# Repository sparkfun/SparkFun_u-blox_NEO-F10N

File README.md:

SparkFun GNSS L1/L5 Breakout- NEO-F10N, SMA
========================================

[*SparkFun GNSS L1/L5 Breakout - NEO-F10N, SMA (GPS-24114)*](https://www.sparkfun.com/products/24114)

The SparkFun GNSS L1/L5 Breakout - NEO-F10N, SMA is a standard precision GNSS board with meter-level positional accuracy. The NEO-F10N uses the L1/L5 bands instead of the more commonly seen L1/L2 bands. Utilizing the L5 band, the NEO-F10N delivers improved performance under challenging urban environments. The L5 signals fall within the protected ARNS (aeronautical radio navigation service) frequency band, leading to less RF interference.

This breakout supports the concurrent reception of three GNSS constellations: GPS, Galileo, and BeiDou. The proprietary dual-band multipath mitigation technology from the u-blox F10 allows the module to choose the best signals from both bands to achieve a significantly better position accuracy in challenging urban environments than with the L1 band alone.

What's different from other u-blox modules is that the NEO-F10N module only supports one serial UART communication port. We included a CH340 USB-to-serial converter to connect the board to a computer's USB port easily. For users connecting the board's serial UART pins to a microcontroller or radio, you will need to cut the USB-TX and USB-RX jumpers to avoid bus contention. Pins for power, serial, pulse per second, and control pins are broken out to 0.1"-spaced pins on the board's edge. We have also conveniently included a 1x6 header should you connect a BlueSMiRF v2 to transmit data wirelessly!

The breakout is also has an on-board rechargeable battery that provides power to the RTC on the NEO-F10N. This reduces the time-to-first fix from a cold start (~28s) to a hot start (2s). The battery will maintain RTC and GNSS orbit data without being connected to power for plenty of time. We have included an SMA connector for a secure connection.

U-blox-based GPS products are configurable using the popular but dense Windows program u-center. Plenty of different functions can be configured on the NEO-F10N: baud rates, update rates, spoofing detection, external interrupts, SBAS, etc. To get started, we've included a few basic UART examples with our SparkFun Arduino Library.

Repository Contents
-------------------
* **.github/workflows** - YAML files used for GitHub Actions and GitHub Pages/mkdocs
* **/Hardware** - KiCad design files (.brd, .sch)
  * **/Production** - Production panel files (.brd)
* **/docs** - Online documentation files
  * **/assets** - Folder containing all the file assets used for product documentation
    * **/3d_model** - Exported 3D models from KiCad
    * **/board_files** - Copy of design files used for product documentation
    * **/component_documentation** - Datasheets and manuals for hardware components
    * **/img** - Images for product documentation
  * **/github** - Files stating how to contribute and filing issues used for product documentation
  * **/javascript** - Folder containing custom javascript used for product documentation
  * **/stylesheet** - Folder containing CSS files used for product documentation
* **/overrides** - Customization files used for product documentation
  * **/.icons** - Icons used for GitHub used for product documentation
  * **./partials** - Used for product documentation

Documentation
--------------
* **[Library](https://github.com/sparkfun/SparkFun_u-blox_GNSS_v3)** - Arduino library for u-blox modules.
* **[Hookup Guide](https://docs.sparkfun.com/SparkFun_u-blox_NEO-F10N)** - Basic hookup guide for the NEO-F10N breakout board.

Product Versions
----------------
* [GPS-24114](https://www.sparkfun.com/products/24114) - Initial release

Version History
---------------
* v1.0 - Initial release

License Information
-------------------

This product is _**open source**_!

Please review the LICENSE.md file for license information.

If you have any questions or concerns on licensing, please contact technical support on our [SparkFun forums](https://forum.sparkfun.com/viewforum.php?f=152).

Distributed as-is; no warranty is given.

- Your friends at SparkFun.

_<COLLABORATION CREDIT>_

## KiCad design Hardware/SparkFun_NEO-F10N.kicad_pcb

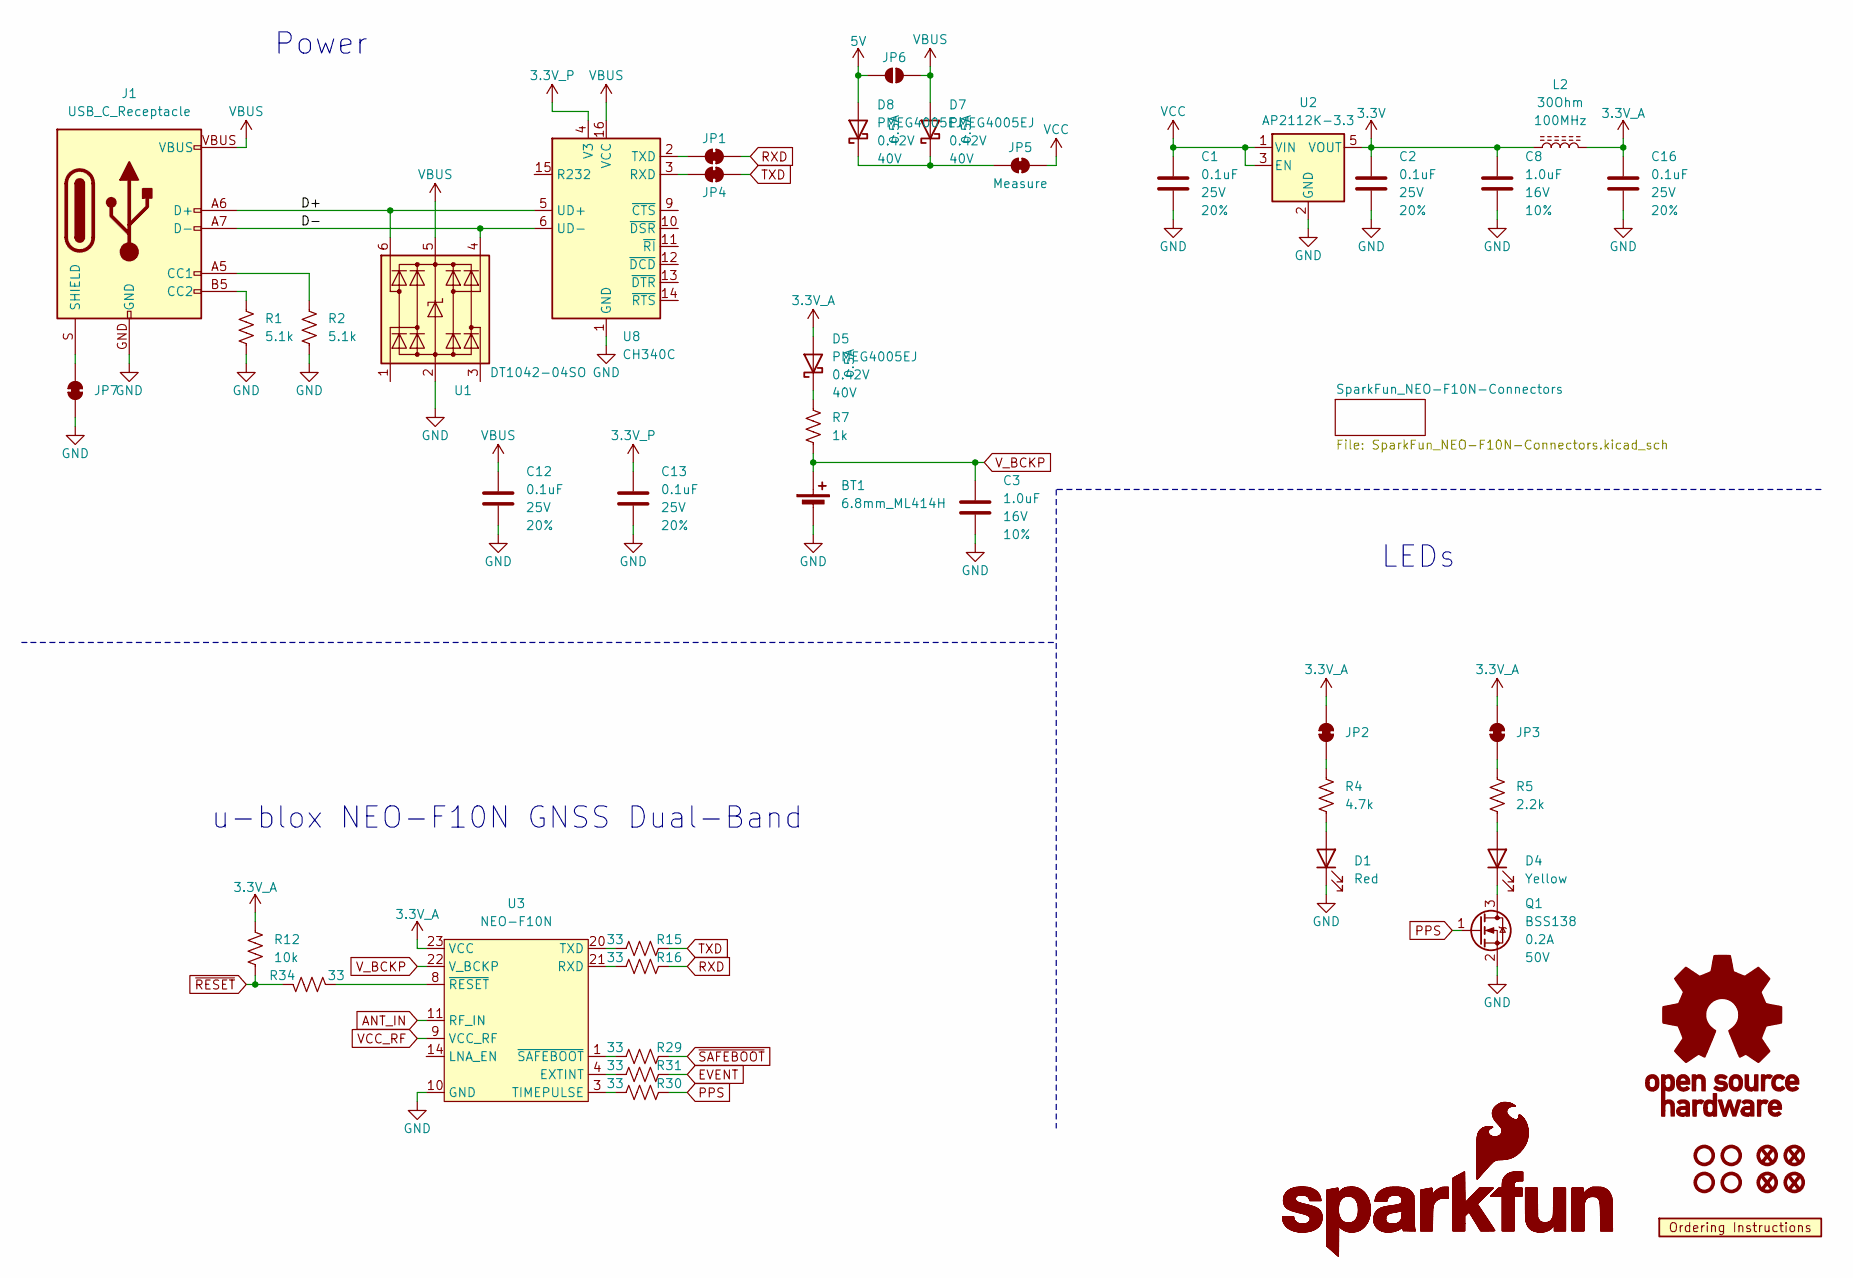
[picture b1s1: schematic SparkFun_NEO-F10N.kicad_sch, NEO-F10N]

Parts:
BT1: 6.8mm_ML414H; ML414H_IV01E
C1, C2, C12, C13, C16: 0.1uF; C_0603_1608Metric; Voltage 25V; Tolerance 20%
C3, C8: 1.0uF; C_0603_1608Metric; Voltage 16V; Tolerance 10%
D1: Red; LED_0603_1608Metric_Red
D4: Yellow; LED_0603_1608Metric_Yellow
D5, D7, D8: PMEG4005EJ; SOD-323
FID1, FID2, FID3, FID4: Fiducial_0.5mm; Fiducial_0.5mm_Mask1mm
G1: OSHW_Logo; Creative_Commons_License
G3, G5: SparkFun_Logo
J1: USB_C_Receptacle; USB-C_16
JP1, JP2, JP3, JP4, JP7: Jumper_2_NC_Trace
JP5: Measure; Jumper_2_PTH_SMD_Combo-NC
JP6: Jumper_2_NO
L2: 30Ohm; C_0603_1608Metric
Q1: BSS138; SOT23-3
R1, R2: 5.1k; R_0603_1608Metric
R4: 4.7k; R_0603_1608Metric
R5: 2.2k; R_0603_1608Metric
R7: 1k; R_0603_1608Metric
R12: 10k; R_0603_1608Metric
R15, R16, R29, R30, R31, R34: 33; R_0603_1608Metric
ST1, ST2, ST3, ST4: Standoff
U1: DT1042-04SO; SOT23-6
U2: AP2112K-3.3; SOT23-5
U3: NEO-F10N; NEO-M9N_M8T_M8U_D9S_F9P_F10N
U7: Ordering_Instructions
U8: CH340C; SO-16

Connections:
3.3V: C2.1, C8.1, L2.1, U2.5 (VOUT); also elsewhere on the board
3.3V_A: C16.1, D5.A, JP2.2 (B), JP3.2 (B), L2.2, R12.1, U3.23 (VCC)
3.3V_P: C13.1, U8.4 (V3)
5V: D8.A, JP6.1 (A); also elsewhere on the board
/D+: J1.A6 (D+), J1.B6 (D+), U1.6 (I/O4), U8.5 (UD+)
/D-: J1.A7 (D-), J1.B7 (D-), U1.4 (I/O3), U8.6 (UD-)
ANT_IN: U3.11 (RF_IN); also elsewhere on the board
EVENT: R31.2; also elsewhere on the board
GND: BT1.-, C1.2, C2.2, C3.2, C8.2, C12.2, C13.2, C16.2, D1.1 (K), J1.GND, JP7.1 (A), Q1.2 (S), R1.2, R2.2, U1.2 (GND), U2.2 (GND), U3.10 (GND), U3.12 (GND), U3.13 (GND), U3.24 (GND), U8.1 (GND); also elsewhere on the board
unnamed: D1.2 (A), R4.2
unnamed: D4.2 (A), R5.2
unnamed: D4.1 (K), Q1.3 (D)
unnamed: D5.C, R7.1
unnamed: J1.A5 (CC1), R2.1
unnamed: J1.B5 (CC2), R1.1
unnamed: J1.S (SHIELD), JP7.2 (B)
unnamed: JP1.1 (A), U8.2 (TXD)
unnamed: JP2.1 (A), R4.1
unnamed: JP3.1 (A), R5.1
unnamed: JP4.1 (A), U8.3 (RXD)
unnamed: D7.C, D8.C, JP5.1 (A)
unnamed: R31.1, U3.4 (EXTINT)
unnamed: R16.1, U3.21 (RXD)
unnamed: R30.1, U3.3 (TIMEPULSE)
unnamed: R15.1, U3.20 (TXD)
unnamed: R34.2, U3.8 (~RESET)
unnamed: R29.1, U3.1 (~SAFEBOOT)
PPS: Q1.1 (G), R30.2; also elsewhere on the board
RXD: JP1.2 (B), R16.2; also elsewhere on the board
TXD: JP4.2 (B), R15.2; also elsewhere on the board
VBUS: C12.1, D7.A, J1.VBUS, JP6.2 (B), U1.5 (VCC), U8.16 (VCC)
VCC: C1.1, JP5.2 (B), U2.1 (VIN), U2.3 (EN)
VCC_RF: U3.9 (VCC_RF); also elsewhere on the board
V_BCKP: BT1.+, C3.1, R7.2, U3.22 (V_BCKP)
~RESET: R12.2, R34.1; also elsewhere on the board
~SAFEBOOT: R29.2; also elsewhere on the board

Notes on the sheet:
LEDs
u-blox NEO-F10N GNSS Dual-Band
Power

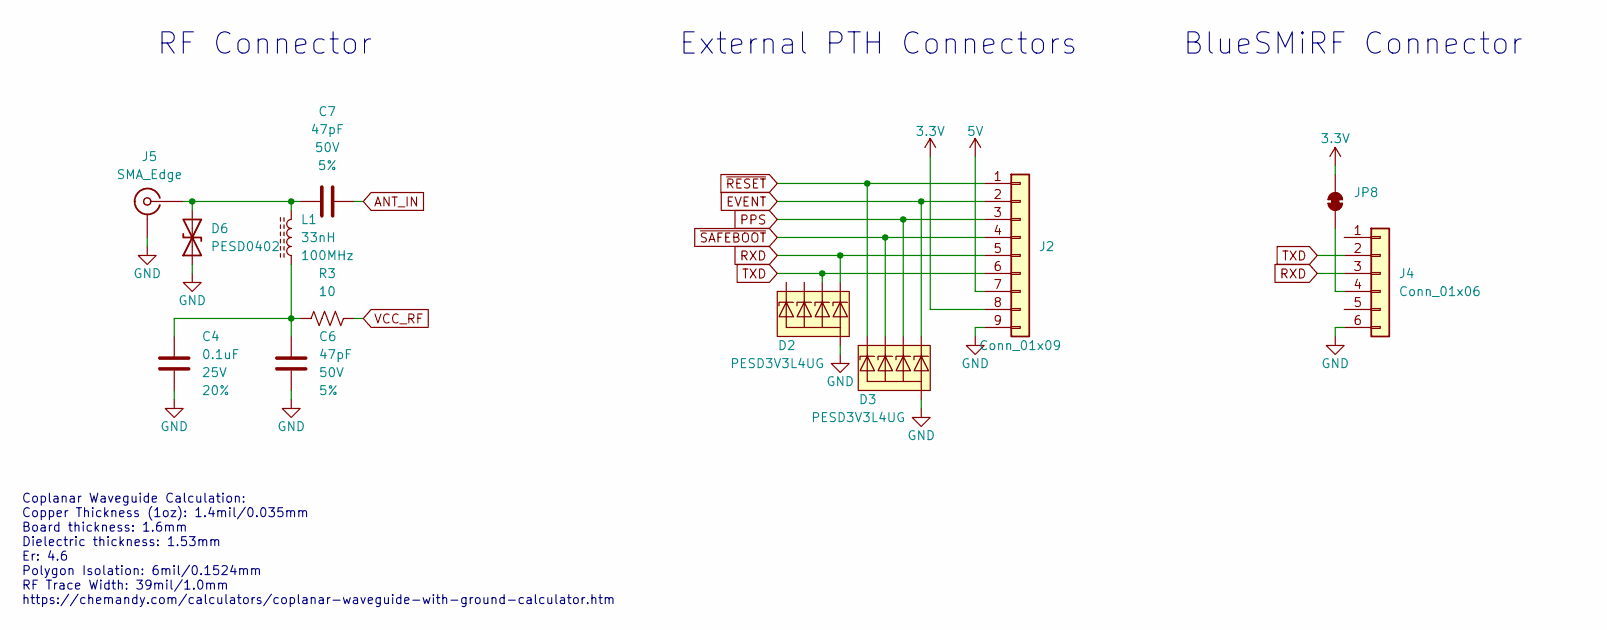
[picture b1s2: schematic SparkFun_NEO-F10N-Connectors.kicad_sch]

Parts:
C4: 0.1uF; C_0603_1608Metric; Voltage 25V; Tolerance 20%
C6, C7: 47pF; C_0603_1608Metric; Voltage 50V; Tolerance 5%
D2, D3: PESD3V3L4UG; SOT-353
D6: PESD0402; C_0402_1005Metric
J2: Conn_01x09; 1x09
J4: Conn_01x06; 1x06
J5: SMA_Edge
JP8: Jumper_2_NC_Trace
L1: 33nH; C_0603_1608Metric
R3: 10; R_0603_1608Metric

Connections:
3.3V: J2.8, JP8.2 (B); also elsewhere on the board
5V: J2.7; also elsewhere on the board
ANT_IN: C7.2; also elsewhere on the board
EVENT: D3.5 (K4), J2.2; also elsewhere on the board
GND: C4.2, C6.2, D2.2 (A), D3.2 (A), D6.1 (A1), J2.9, J4.6, J5.2 (Ext); also elsewhere on the board
unnamed: C4.1, C6.1, L1.1, R3.1
unnamed: C7.1, D6.2 (A2), J5.1 (In), L1.2
unnamed: J4.4, JP8.1 (A)
PPS: D3.4 (K3), J2.3; also elsewhere on the board
RXD: D2.5 (K4), J2.5, J4.3; also elsewhere on the board
TXD: D2.4 (K3), J2.6, J4.2; also elsewhere on the board
VCC_RF: R3.2; also elsewhere on the board
~RESET: D3.1 (K1), J2.1; also elsewhere on the board
~SAFEBOOT: D3.3 (K2), J2.4; also elsewhere on the board

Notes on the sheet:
External PTH Connectors
Coplanar Waveguide Calculation: Copper Thickness (1oz): 1.4mil/0.035mm Board thickness: 1.6mm Dielectric thickness: 1.53mm Er: 4.6 Polygon Isolation: 6mil/0.1524mm RF Trace Width: 39mil/1.0mm https://chemandy.com/calculators/coplanar-waveguide-with-ground-calculator.htm
RF Connector
BlueSMiRF Connector

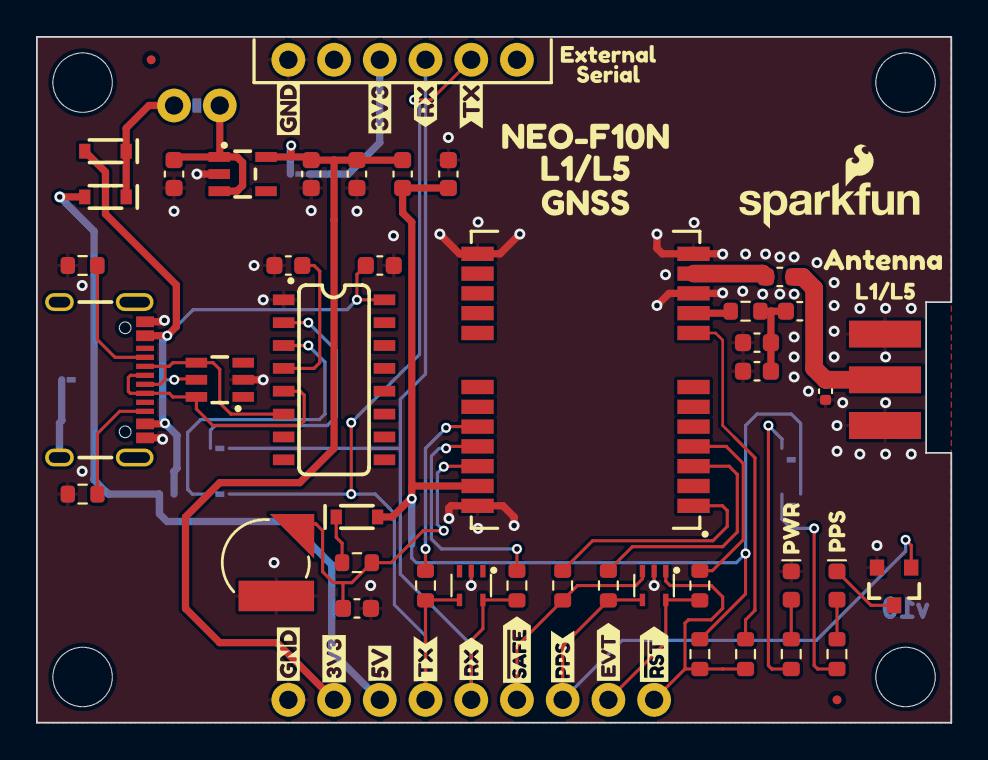
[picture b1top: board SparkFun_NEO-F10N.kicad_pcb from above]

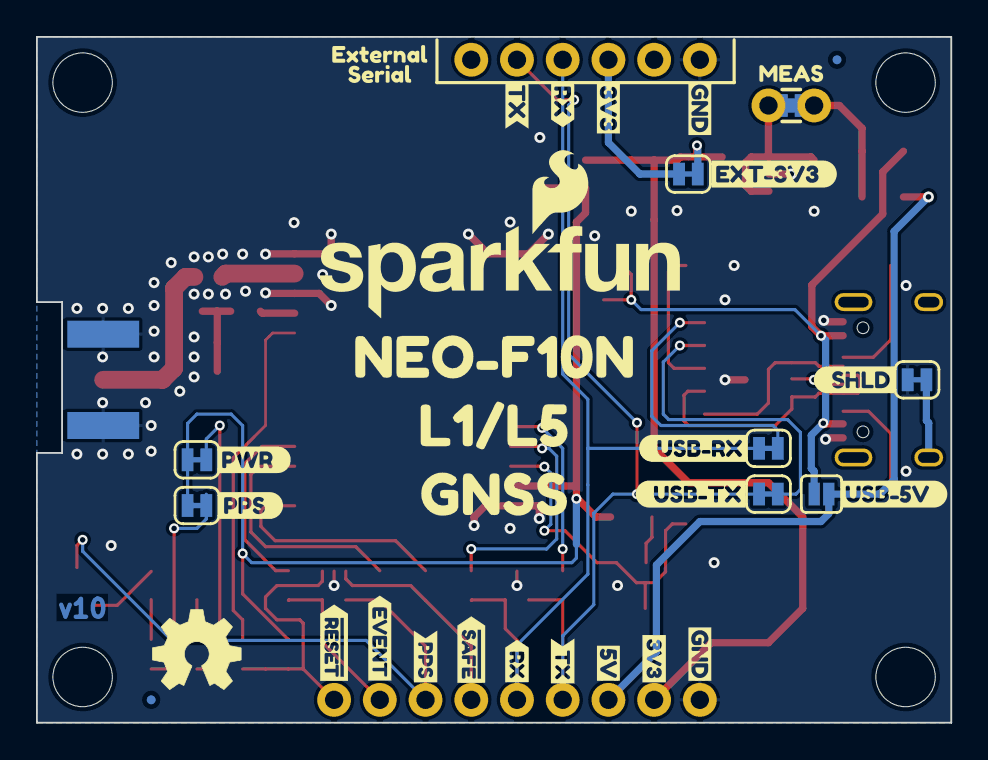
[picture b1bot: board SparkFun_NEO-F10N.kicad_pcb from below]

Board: 2 copper layers, 50.8 x 38.1 mm, 110 parts (37 on the bottom side), 39 nets.

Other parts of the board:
Ref**: Val**; OSHW_Logo_5mm
kibuzzard-64C2E6A3: G***; kibuzzard-64C2E6A3
kibuzzard-64C2E6BD: G***; kibuzzard-64C2E6BD
kibuzzard-64C2EB16: G***; kibuzzard-64C2EB16
kibuzzard-64D296AE: G***; kibuzzard-64D296AE
kibuzzard-64E773DA, kibuzzard-64E773DA#2: G***; kibuzzard-64E773DA
kibuzzard-64E774E1: G***; kibuzzard-64E774E1
kibuzzard-64E774E7: G***; kibuzzard-64E774E7
kibuzzard-64E774EF: G***; kibuzzard-64E774EF
kibuzzard-64E774F5: G***; kibuzzard-64E774F5
kibuzzard-654D4A62: G***; kibuzzard-654D4A62
kibuzzard-654D4E9F: G***; kibuzzard-654D4E9F
kibuzzard-654D4E65: G***; kibuzzard-654D4E65
kibuzzard-654D4E82: G***; kibuzzard-654D4E82
kibuzzard-654D4EBD: G***; kibuzzard-654D4EBD
kibuzzard-654D22C2, kibuzzard-654D22C2#2: G***; kibuzzard-654D22C2
kibuzzard-654D22ED: G***; kibuzzard-654D22ED
kibuzzard-654D22FF: G***; kibuzzard-654D22FF
kibuzzard-654D24A3: G***; kibuzzard-654D24A3
kibuzzard-654D24AA: G***; kibuzzard-654D24AA
kibuzzard-654D24CA: G***; kibuzzard-654D24CA
kibuzzard-654D232B: G***; kibuzzard-654D232B
kibuzzard-654D2357: G***; kibuzzard-654D2357
kibuzzard-655A6C20: G***; kibuzzard-655A6C20
kibuzzard-655A6C73: G***; kibuzzard-655A6C73
kibuzzard-655A6CC4: G***; kibuzzard-655A6CC4
kibuzzard-655A6CE2: G***; kibuzzard-655A6CE2
kibuzzard-6542D1F0: G***; kibuzzard-6542D1F0
kibuzzard-6542D1FC: G***; kibuzzard-6542D1FC
kibuzzard-6542D20F: G***; kibuzzard-6542D20F
kibuzzard-6542D208: G***; kibuzzard-6542D208
kibuzzard-6598A013: G***; kibuzzard-6598A013
kibuzzard-6598A076: G***; kibuzzard-6598A076
kibuzzard-65989F3D: G***; kibuzzard-65989F3D
kibuzzard-65989F89: G***; kibuzzard-65989F89
kibuzzard-65989F92: G***; kibuzzard-65989F92
kibuzzard-650880E6: G***; kibuzzard-650880E6
kibuzzard-659876FC: G***; kibuzzard-659876FC
kibuzzard-6598770D: G***; kibuzzard-6598770D
kibuzzard-6598978C: G***; kibuzzard-6598978C
kibuzzard-6598994F, kibuzzard-6598994F#2: G***; kibuzzard-6598994F
kibuzzard-65989731, kibuzzard-65989731#2: G***; kibuzzard-65989731
kibuzzard-65989781: G***; kibuzzard-65989781
kibuzzard-65989942, kibuzzard-65989942#2: G***; kibuzzard-65989942

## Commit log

2023-11-13 Remove backup files
2023-11-19 Update datasheet links
2023-11-19 Add bars to RESET and SAFE labels
2023-11-19 Compress schematic
2023-11-21 Add the public docs
2024-01-09 Update layout and panel files post design review.
2024-03-13 Push Initial Tutorial to GitHub Pages and Update Revised u-blox Documents
2024-03-21 Include Example 12 to View Coordinates and Product Showcase Video
2024-04-01 Deployed 7698f3e with MkDocs version: 1.5.3
2024-07-02 Remove Hide Attribute so that I can show in Single Page View
2024-07-02 Update hardware_hookup.md
    Adjust colors to match wire color since it is hard to see connection from zooming in
2024-07-02 Deployed dde13ea with MkDocs version: 1.6.0
2024-08-19 Update 3D models
2024-09-06 Deployed 2ed63c9 with MkDocs version: 1.6.1
2024-10-28 Add cookies and fix html tag
2024-10-29 Deployed 43e5896 with MkDocs version: 1.6.1
2024-11-14 Add 3D Model
2024-11-15 Remove STL File
2024-11-15 Deployed c63dac4 with MkDocs version: 1.6.1
2024-12-10 Update 3D Model with KiCad Library
    USB C and SMA connector were not linked with the latest SparkFun KiCad Library
2024-12-10 Deployed 0697cf1 with MkDocs version: 1.6.1
2025-02-20 Update introduction.md
    Fixing missing image
2025-02-20 Deployed 8cdc436 with MkDocs version: 1.6.1
2025-09-11 Remove git-authors
2026-06-03 Deployed 398e16d with MkDocs version: 1.6.1

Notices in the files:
parts and their libraries:
Released under the Creative Commons Attribution Share-Alike 4.0 License
https://creativecommons.org/licenses/by-sa/4.0
